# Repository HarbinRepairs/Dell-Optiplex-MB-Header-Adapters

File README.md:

# Front Panel Header Adapters for Dell Optiplex Motherboards

Get it at our store:

https://store.harbinrepairs.com/index.php/product/dell-optiplex-390-3010-3020-front-panel-header-adapter-3pc-kit/

https://store.harbinrepairs.com/index.php/product/dell-5-6-pin-power-button-led-panel-adapter/

Get it on eBay:

https://www.ebay.com/itm/264638815586

https://www.ebay.com/itm/264638806788

## License
Harbin Repairs 2020
Creative Commons Attribution ShareAlike 4.0
https://creativecommons.org/licenses/by-sa/4.0/

GNU General Public License v3.0

Harbin Repairs is not affiliated with Dell in any way shape or form.

## Documentation

This kit is designed for the mid tower (not SFF or small form factor) desktops. It allows you to connect standard PC case front panel headers to the Dell Optiplex 390, 3010, and 3020 motherboards. These are often used to build budget gaming PC’s using decommissioned office desktops and convert them to work with modern PC cases. WARNING! Connecting these adapters in the wrong orientation or with the wrong models could result in damage to your motherboard. Do not use these adapters with models other than the ones mentioned above and make sure to check out our assembly video below.

### Installation Guide Video

https://www.youtube.com/watch?v=3fb6-B5Ux_s

### Compatibility

The three piece adapter kit is only compatibile with the Dell optiplex 390, 3010, and 3020 DT & MT Dekstops. It will not work on the SFF desktops since they use a different connector and are not ideal since they do not have a removable I/O shield. The 5/6 pin power button however may work with most dell desktops that have a 5/6 pin header for the front panel power button/LED.

### Bill of Materials

| Qty | Description                                    | Aliexpress             | eBay Links (Affiliate)  | Amazon Links (Affiliate) |
|-----|------------------------------------------------|------------------------|-------------------------|--------------------------|
| 3   | PCB                                            | Manufacturer of choice |                         |                          |
| 1   | 2x3 2mm 6pin Female Straight THT Connector     | http://bit.ly/2SQY12E  | https://ebay.to/2P2j5lk | N/A                      |
| 1   | 2x5 2.54mm 10pin Female Straight THT Connector | http://bit.ly/3bOo6ru  | https://ebay.to/2ubbdXK | https://amzn.to/2u3uMky  |
| 1   | 2x8 2.54mm 16pin Female Straight THT Connector | http://bit.ly/39JsCpE  | https://ebay.to/2SA2zeA | https://amzn.to/2Hwy3Mr  |
| 1   | 1x40 2.54mm Male Pin Header THT                | http://bit.ly/2HzO3NS  | https://ebay.to/2V6OmYa | https://amzn.to/38CYH2a  |
| 4   | 0805 SMD Yellow LED                            | http://bit.ly/38DWLGB  | https://ebay.to/2UW0tHL | https://amzn.to/38CjiUj  |
| 5   | 0805 SMD 470Ω Resistor                         | http://bit.ly/2SOXqOO  | https://ebay.to/38CF7D5 | https://amzn.to/38E2ThY  |

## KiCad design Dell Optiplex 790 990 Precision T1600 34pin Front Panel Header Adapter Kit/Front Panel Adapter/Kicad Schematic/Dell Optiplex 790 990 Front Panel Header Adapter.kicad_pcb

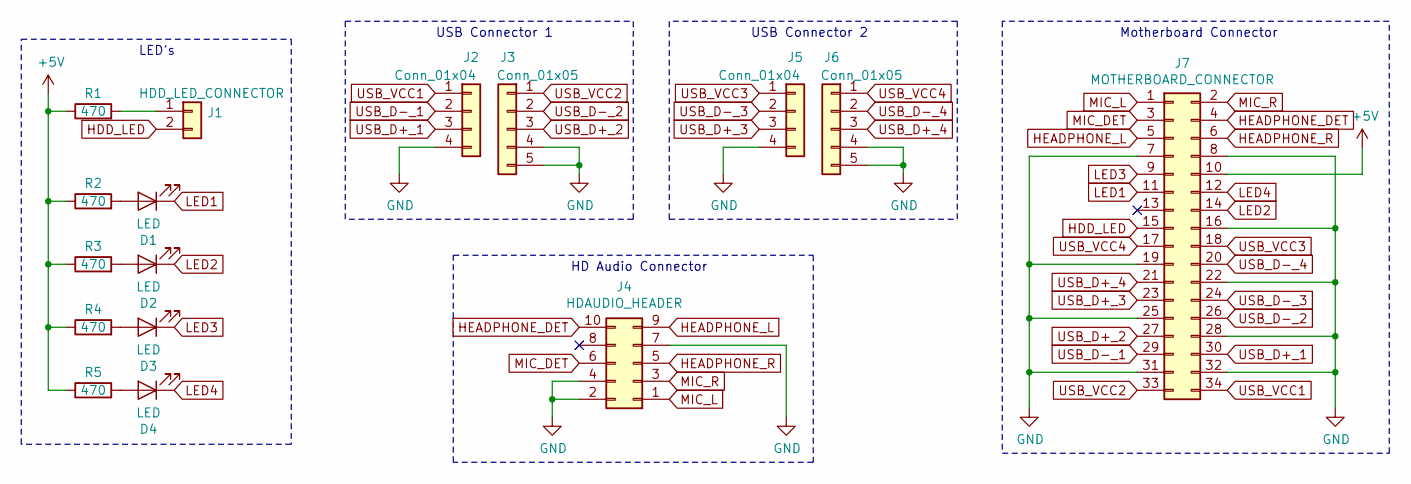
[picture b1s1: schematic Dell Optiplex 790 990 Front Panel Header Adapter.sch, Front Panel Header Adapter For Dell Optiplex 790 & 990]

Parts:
D1, D2, D3, D4: LED; LED_0805_2012Metric
J1: HDD_LED_CONNECTOR; PinHeader_1x02_P2.54mm_Vertical
J2, J5: Conn_01x04; PinHeader_1x04_P2.54mm_Vertical
J3, J6: Conn_01x05; PinHeader_1x05_P2.54mm_Vertical
J4: HDAUDIO_HEADER; PinHeader_2x05_P2.54mm_Vertical
J7: MOTHERBOARD_CONNECTOR; PinSocket_2x17_P2.00mm_Vertical
R1, R2, R3, R4, R5: 470; R_0805_2012Metric

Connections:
+5V: J7.10, R1.1, R2.1, R3.1, R4.1, R5.1
GND: J2.4, J3.4, J3.5, J4.2, J4.4, J4.7, J5.4, J6.4, J6.5, J7.7, J7.8, J7.16, J7.19, J7.22, J7.25, J7.28, J7.31, J7.32
HDD_LED: J1.2, J7.15
HEADPHONE_DET: J4.10, J7.4
HEADPHONE_L: J4.9, J7.5
HEADPHONE_R: J4.5, J7.6
LED1: D1.1 (K), J7.11
LED2: D2.1 (K), J7.14
LED3: D3.1 (K), J7.9
LED4: D4.1 (K), J7.12
MIC_DET: J4.6, J7.3
MIC_L: J4.1, J7.1
MIC_R: J4.3, J7.2
unnamed: D1.2 (A), R2.2
unnamed: D2.2 (A), R3.2
unnamed: D3.2 (A), R4.2
unnamed: D4.2 (A), R5.2
unnamed: J1.1, R1.2
USB_D+_1: J2.3, J7.30
USB_D+_2: J3.3, J7.27
USB_D+_3: J5.3, J7.23
USB_D+_4: J6.3, J7.21
USB_D-_1: J2.2, J7.29
USB_D-_2: J3.2, J7.26
USB_D-_3: J5.2, J7.24
USB_D-_4: J6.2, J7.20
USB_VCC1: J2.1, J7.34
USB_VCC2: J3.1, J7.33
USB_VCC3: J5.1, J7.18
USB_VCC4: J6.1, J7.17

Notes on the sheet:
USB Connector 1
USB Connector 2
HD Audio Connector
LED’s
Motherboard Connector

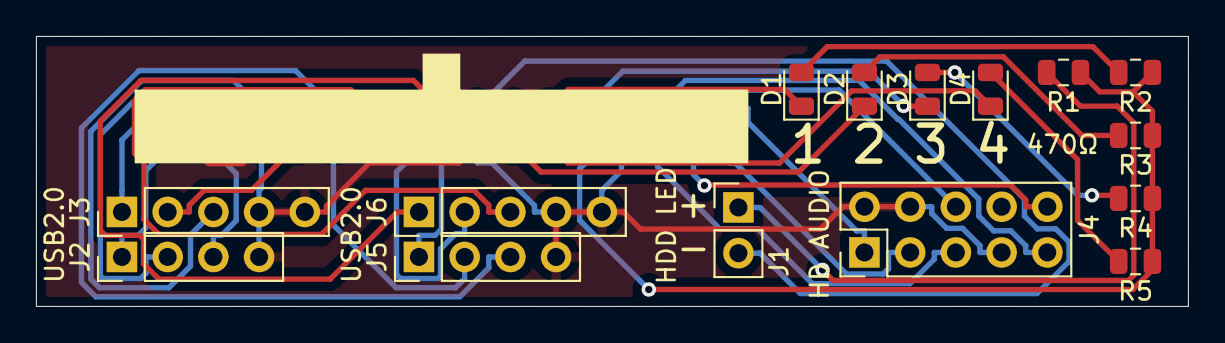
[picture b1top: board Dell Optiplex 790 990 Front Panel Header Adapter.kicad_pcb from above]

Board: 2 copper layers, 64.0 x 15.0 mm, 16 parts (1 on the bottom side), 30 nets.

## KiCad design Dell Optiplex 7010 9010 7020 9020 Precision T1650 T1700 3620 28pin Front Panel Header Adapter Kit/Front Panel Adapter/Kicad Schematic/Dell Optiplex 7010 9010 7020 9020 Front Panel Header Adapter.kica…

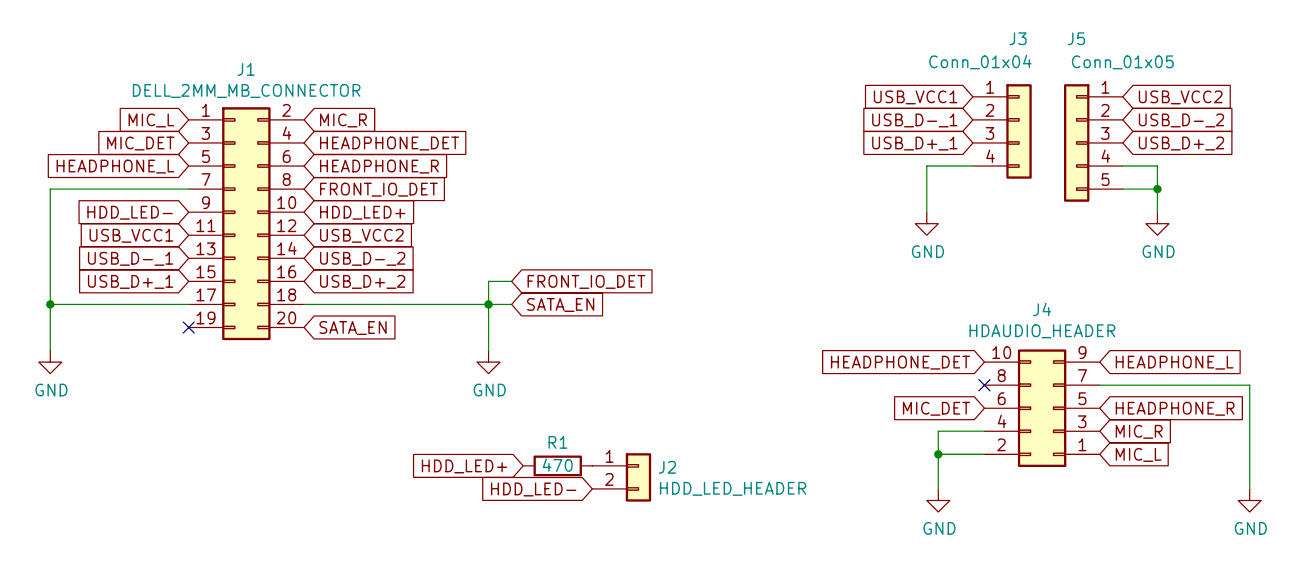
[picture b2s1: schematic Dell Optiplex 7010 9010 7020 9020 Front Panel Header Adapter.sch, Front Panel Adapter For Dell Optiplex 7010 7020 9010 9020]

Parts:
J1: DELL_2MM_MB_CONNECTOR; PinSocket_2x10_P2.00mm_Vertical
J2: HDD_LED_HEADER; PinHeader_1x02_P2.54mm_Vertical
J3: Conn_01x04; PinHeader_1x04_P2.54mm_Vertical
J4: HDAUDIO_HEADER; PinHeader_2x05_P2.54mm_Vertical
J5: Conn_01x05; PinHeader_1x05_P2.54mm_Vertical
R1: 470; R_0805_2012Metric

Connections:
FRONT_IO_DET: J1.7, J1.8, J1.17, J1.18, J1.20, J3.4, J4.2, J4.4, J4.7, J5.4, J5.5
HDD_LED+: J1.10, R1.1
HDD_LED-: J1.9, J2.2
HEADPHONE_DET: J1.4, J4.10
HEADPHONE_L: J1.5, J4.9
HEADPHONE_R: J1.6, J4.5
MIC_DET: J1.3, J4.6
MIC_L: J1.1, J4.1
MIC_R: J1.2, J4.3
unnamed: J2.1, R1.2
USB_D+_1: J1.15, J3.3
USB_D+_2: J1.16, J5.3
USB_D-_1: J1.13, J3.2
USB_D-_2: J1.14, J5.2
USB_VCC1: J1.11, J3.1
USB_VCC2: J1.12, J5.1

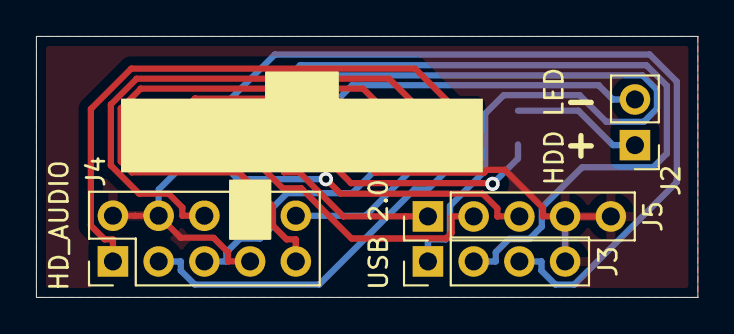
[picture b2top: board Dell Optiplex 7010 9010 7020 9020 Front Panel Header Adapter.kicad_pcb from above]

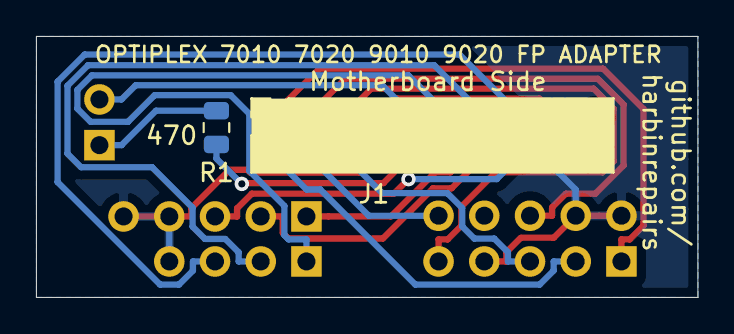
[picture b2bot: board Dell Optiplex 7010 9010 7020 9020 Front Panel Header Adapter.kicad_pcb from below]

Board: 2 copper layers, 36.8 x 14.5 mm, 6 parts (2 on the bottom side), 16 nets.

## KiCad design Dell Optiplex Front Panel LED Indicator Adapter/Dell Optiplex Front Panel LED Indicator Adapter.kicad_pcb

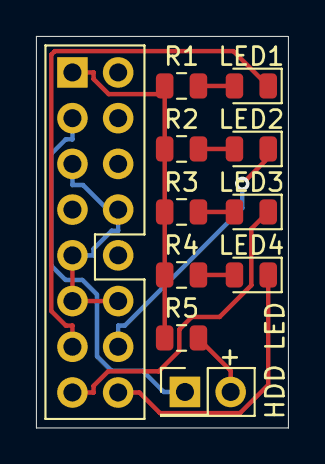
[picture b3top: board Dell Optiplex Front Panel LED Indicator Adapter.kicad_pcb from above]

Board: 2 copper layers, 14.0 x 21.8 mm, 11 parts (1 on the bottom side), 12 nets.

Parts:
D1: LED1; LED_0805_2012Metric
D2: LED2; LED_0805_2012Metric
D3: LED3; LED_0805_2012Metric
D4: LED4; LED_0805_2012Metric
J1: MB Connector; PinSocket_2x08_P2.54mm_Vertical
J2: HDD LED; PinHeader_2x01_P2.54mm_Vertical
R1, R2, R3, R4, R5: 470; R_0805_2012Metric

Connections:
HDD_LED: J1.3, J2.1
LED1: D1.1, J1.13
LED2: D2.1, J1.14
LED3: D3.1, J1.15
LED4: D4.1, J1.16
unnamed: D1.2, R1.2
unnamed: D2.2, R2.2
unnamed: D3.2, R3.2
unnamed: D4.2, R4.2
unnamed: J2.2, R5.2
SENSE_JUMPER: J1.5, J1.8, J1.9, J1.11, J1.12
VCC: J1.1, R1.1, R2.1, R3.1, R4.1, R5.1

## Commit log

2019-11-17 Create LICENSE
2023-02-11 Fix pdf path on windows
    Windows paths cannot have `:` in them
2023-02-11 rename all the other problematic paths
